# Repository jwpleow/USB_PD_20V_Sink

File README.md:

## USB PD 20V/3A Sink

A simple USB Type C PD board to request 20V/3A, using the CYPD3177.

Mostly a copy of https://github.com/ElectronicCats/Cat-Sink

BOM and CPL are ready for manufacturing with JLCPCB.

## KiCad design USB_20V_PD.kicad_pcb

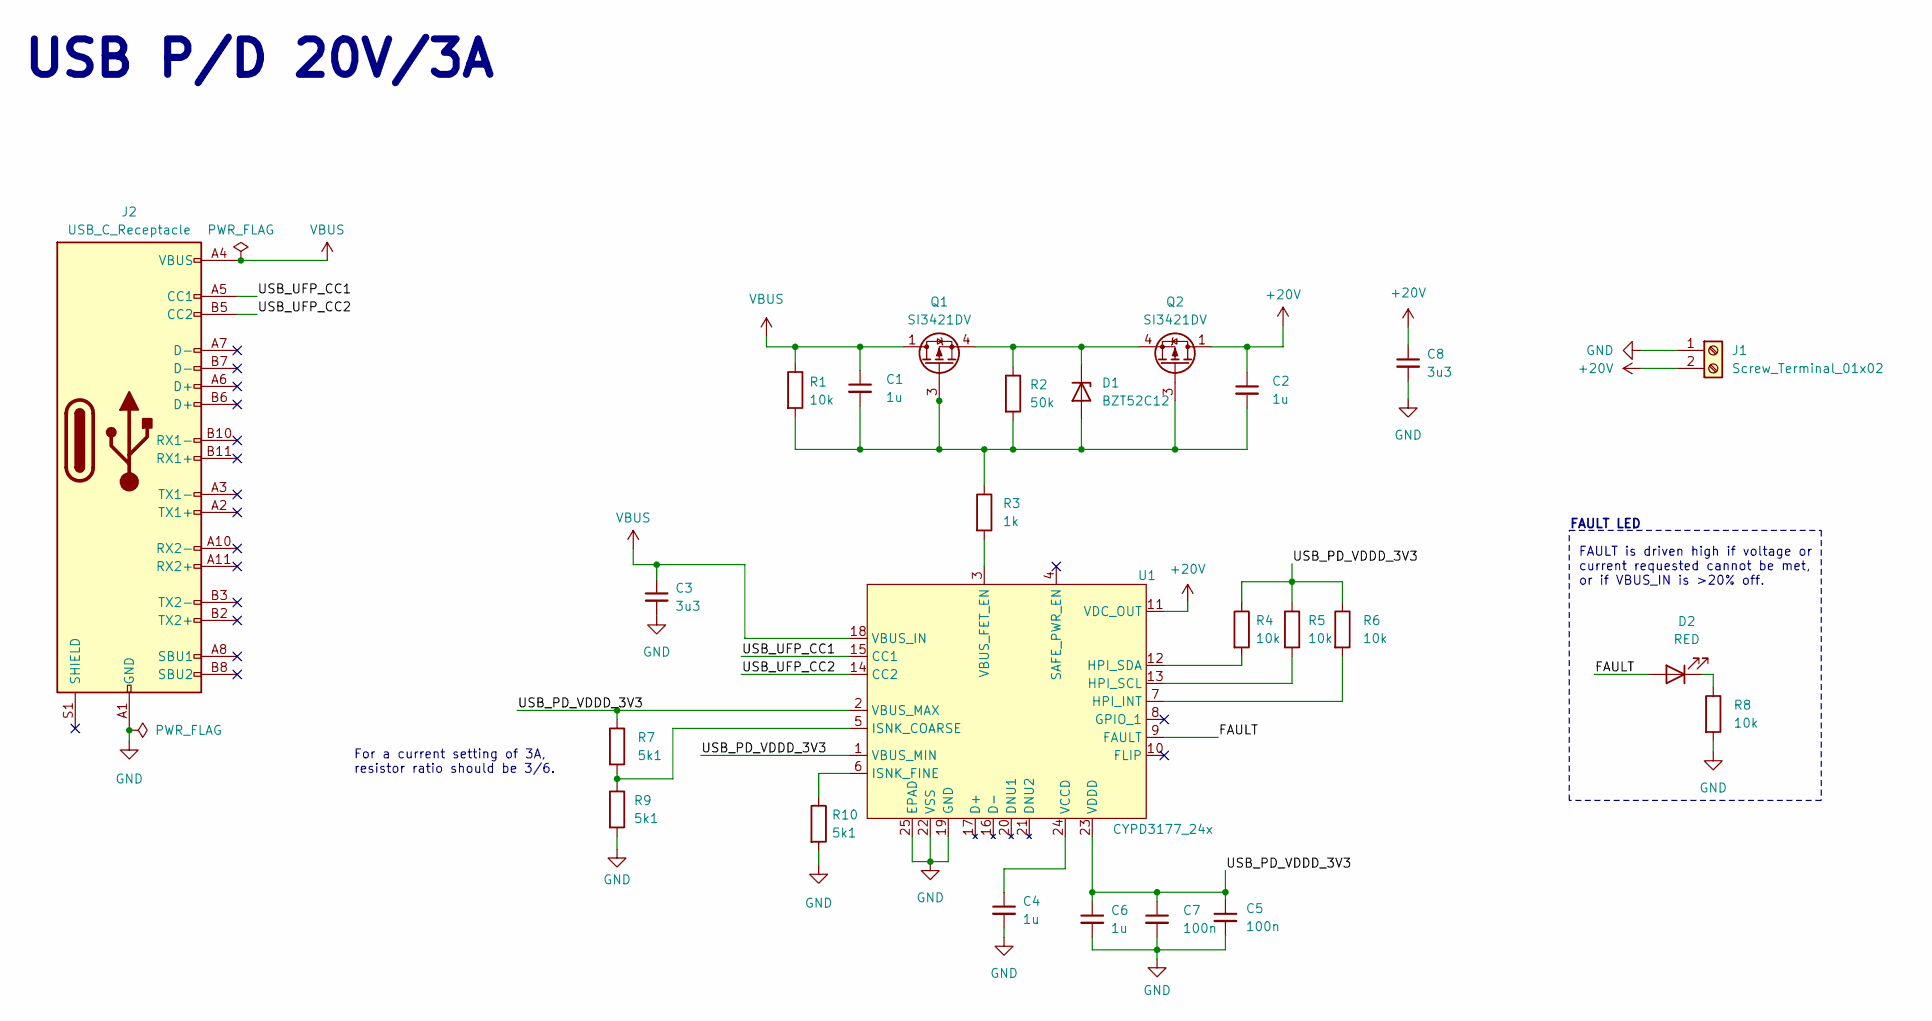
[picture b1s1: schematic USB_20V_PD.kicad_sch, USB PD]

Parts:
C1, C2, C4, C6: 1u; C_0603_1608Metric
C3, C8: 3u3; C_0603_1608Metric
C5, C7: 100n; C_0603_1608Metric
D1: BZT52C12; D_SOD-123
D2: RED; LED_0603_1608Metric
J1: Screw_Terminal_01x02; TerminalBlock_Phoenix_MKDS-1,5-2-5.08_1x02_P5.08mm_Horizont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
J2: USB_C_Receptacle; USB_C_Receptacle_GT-USB-7052
Q1, Q2: SI3421DV; SOT-23-6
R1, R4, R5, R6, R8: 10k; R_0603_1608Metric
R2: 50k; R_0603_1608Metric
R3: 1k; R_0603_1608Metric
R7, R9, R10: 5k1; R_0603_1608Metric
U1: CYPD3177_24x; CYPD3177_24LQx_QFN-24_EP_4x4_Pitch0.5mm

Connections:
+20V: C2.1, C8.1, J1.2, Q2.1 (D), Q2.2 (D1), Q2.5 (D2), Q2.6 (D3), U1.11 (VDC_OUT)
/FAULT: D2.2 (A), U1.9 (FAULT)
/USB_PD_VDDD_3V3: C5.1, C6.1, C7.1, R4.1, R5.1, R6.1, R7.1, U1.1 (VBUS_MIN), U1.2 (VBUS_MAX), U1.23 (VDDD)
/USB_UFP_CC1: J2.A5 (CC1), U1.15 (CC1)
/USB_UFP_CC2: J2.B5 (CC2), U1.14 (CC2)
GND: C3.2, C4.2, C5.2, C6.2, C7.2, C8.2, J1.1, J2.A1 (GND), J2.A12 (GND), J2.B1 (GND), J2.B12 (GND), R8.2, R9.2, R10.2, U1.19 (GND), U1.22 (VSS), U1.25 (EPAD)
unnamed: C1.2, C2.2, D1.2 (A), Q1.3 (G), Q2.3 (G), R1.2, R2.2, R3.1
unnamed: D1.1 (K), Q1.4 (S), Q2.4 (S), R2.1
unnamed: D2.1 (K), R8.1
unnamed: R6.2, U1.7 (HPI_INT)
unnamed: R5.2, U1.13 (HPI_SCL)
unnamed: R4.2, U1.12 (HPI_SDA)
unnamed: R7.2, R9.1, U1.5 (ISNK_COARSE)
unnamed: R10.1, U1.6 (ISNK_FINE)
unnamed: R3.2, U1.3 (VBUS_FET_EN)
unnamed: C4.1, U1.24 (VCCD)
VBUS: C1.1, C3.1, J2.A4 (VBUS), J2.A9 (VBUS), J2.B4 (VBUS), J2.B9 (VBUS), Q1.1 (D), Q1.2 (D1), Q1.5 (D2), Q1.6 (D3), R1.1, U1.18 (VBUS_IN)

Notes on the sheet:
FAULT is driven high if voltage or current requested cannot be met, or if VBUS_IN is >20% off.
USB P/D 20V/3A
FAULT LED
For a current setting of 3A, resistor ratio should be 3/6.

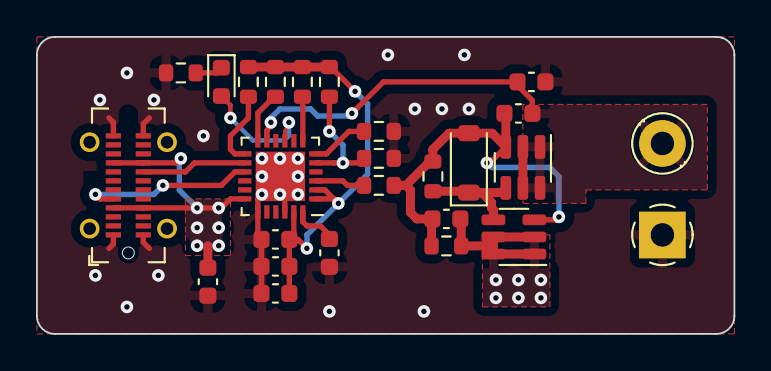
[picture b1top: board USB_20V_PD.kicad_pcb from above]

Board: 2 copper layers, 38.8 x 16.5 mm, 25 parts (0 on the bottom side), 17 nets.

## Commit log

2024-01-22 done
2024-02-01 update readme and schematics
